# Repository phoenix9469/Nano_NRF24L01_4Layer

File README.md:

## Arduino Nano with DC-DC Converter and NRF24L01 2.4G RF module

### Power IN
XL1509-5.0, Support 5V~45V DC IN  
Reverse Volatege Protection
### Arduino Nano
Atmega328P-AU,FT232RL USB TO UART(USB TYPE C)
### RF module
NORDIC NRF24L01 Transceiver  
SPI communication with Atmega328p  
IPEX antenna connector

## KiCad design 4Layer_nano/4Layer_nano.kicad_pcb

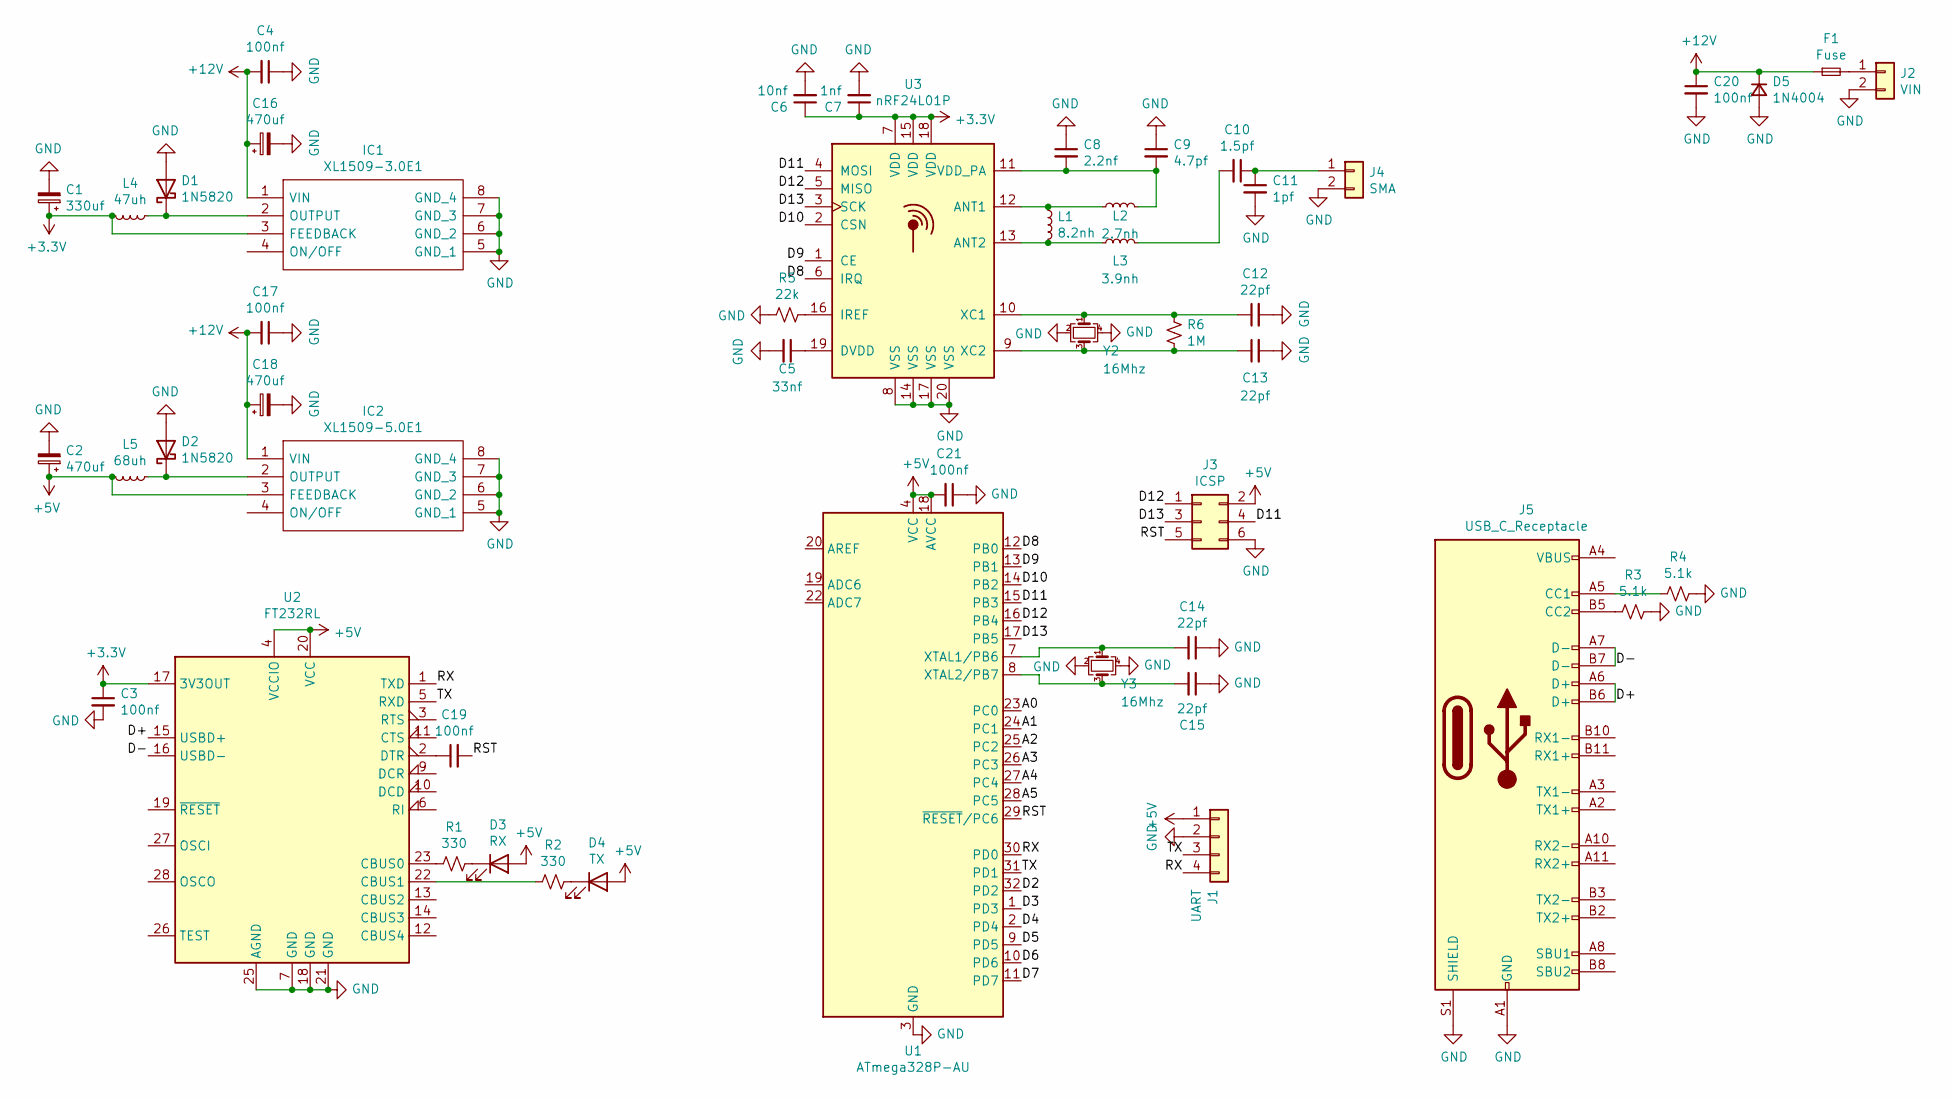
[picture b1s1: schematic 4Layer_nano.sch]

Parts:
C1: 330uf; CP_EIA-7343-31_Kemet-D
C2, C16, C18: 470uf; CP_EIA-7343-31_Kemet-D
C3, C4, C17, C19, C20, C21: 100nf; C_0603_1608Metric
C5: 33nf; C_0402_1005Metric
C6: 10nf; C_0402_1005Metric
C7: 1nf; C_0402_1005Metric
C8: 2.2nf; C_0402_1005Metric
C9: 4.7pf; C_0402_1005Metric
C10: 1.5pf; C_0402_1005Metric
C11: 1pf; C_0402_1005Metric
C12, C13: 22pf; C_0402_1005Metric
C14, C15: 22pf; C_0603_1608Metric
D1, D2: 1N5820; D_SMA
D3: RX; LED_0603_1608Metric
D4: TX; LED_0603_1608Metric
D5: 1N4004; D_SMA
F1: Fuse; FUSC6127X269N
IC1: XL1509-3.0E1; SOIC127P600X175-8N; Manufacturer_Part_Number XL1509-5.0E1
IC2: XL1509-5.0E1; SOIC127P600X175-8N; Manufacturer_Part_Number XL1509-5.0E1
J1: UART; PinHeader_1x04_P2.54mm_Vertical
J2: VIN; TerminalBlock_TE_282834-2_1x02_P2.54mm_Horizontal
J3: ICSP; PinHeader_2x03_P2.54mm_Vertical
J4: SMA; U.FL_Hirose_U.FL-R-SMT-1_Vertical
J5: USB_C_Receptacle; USB_C_Receptacle_HRO_TYPE-C-31-M-12
L1: 8.2nh; L_0402_1005Metric
L2: 2.7nh; L_0402_1005Metric
L3: 3.9nh; L_0402_1005Metric
L4: 47uh; inductor 77
L5: 68uh; inductor 77
R1, R2: 330; R_0603_1608Metric
R3, R4: 5.1k; R_0603_1608Metric
R5: 22k; R_0402_1005Metric
R6: 1M; R_0402_1005Metric
U1: ATmega328P-AU; TQFP-32_7x7mm_P0.8mm
U2: FT232RL; SSOP-28_5.3x10.2mm_P0.65mm
U3: nRF24L01P; QFN-20-1EP_4x4mm_P0.5mm_EP2.5x2.5mm
Y2, Y3: 16Mhz; Crystal_SMD_3225-4Pin_3.2x2.5mm

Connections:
+3V3: C1.1, C3.1, C6.1, C7.1, IC1.3 (FEEDBACK), L4.2, U2.17 (3V3OUT), U3.7 (VDD), U3.15 (VDD), U3.18 (VDD)
+5V: C2.1, C21.2, D3.2 (A), D4.2 (A), IC2.3 (FEEDBACK), J1.1, J3.2, L5.2, U1.4 (VCC), U1.6 (VCC), U1.18 (AVCC), U2.4 (VCCIO), U2.20 (VCC)
+12V: C4.2, C16.1, C17.2, C18.1, C20.1, D5.1 (K), F1.1, IC1.1 (VIN), IC2.1 (VIN)
/A0: U1.23 (PC0)
/A1: U1.24 (PC1)
/A2: U1.25 (PC2)
/A3: U1.26 (PC3)
/A4: U1.27 (PC4)
/A5: U1.28 (PC5)
/D2: U1.32 (PD2)
/D3: U1.1 (PD3)
/D4: U1.2 (PD4)
/D5: U1.9 (PD5)
/D6: U1.10 (PD6)
/D7: U1.11 (PD7)
/D8: U1.12 (PB0), U3.6 (IRQ)
/D9: U1.13 (PB1), U3.1 (CE)
/D10: U1.14 (PB2), U3.2 (CSN)
/D11: J3.4, U1.15 (PB3), U3.4 (MOSI)
/D12: J3.1, U1.16 (PB4), U3.5 (MISO)
/D13: J3.3, U1.17 (PB5), U3.3 (SCK)
/D+: J5.A6 (D+), J5.B6 (D+), U2.15 (USBD+)
/D-: J5.A7 (D-), J5.B7 (D-), U2.16 (USBD-)
/RST: C19.2, J3.5, U1.29 (~RESET~/PC6)
/RX: J1.4, U1.30 (PD0), U2.1 (TXD)
/TX: J1.3, U1.31 (PD1), U2.5 (RXD)
GND: C1.2, C2.2, C3.2, C4.1, C5.2, C6.2, C7.2, C8.1, C9.1, C11.2, C12.2, C13.2, C14.1, C15.1, C16.2, C17.1, C18.2, C20.2, C21.1, D1.2 (A), D2.2 (A), D5.2 (A), IC1.5 (GND_1), IC1.6 (GND_2), IC1.7 (GND_3), IC1.8 (GND_4), IC2.5 (GND_1), IC2.6 (GND_2), IC2.7 (GND_3), IC2.8 (GND_4), J1.2, J2.2, J3.6, J4.2, J5.A1 (GND), J5.A12 (GND), J5.B1 (GND), J5.B12 (GND), J5.S1 (SHIELD), R3.1, R4.1, R5.1, U1.3 (GND), U1.5 (GND), U1.21 (GND), U2.7 (GND), U2.18 (GND), U2.21 (GND), U2.25 (AGND), U3.8 (VSS), U3.14 (VSS), U3.17 (VSS), U3.20 (VSS), Y2.2, Y2.4, Y3.2, Y3.4
unnamed: C5.1, U3.19 (DVDD)
unnamed: C8.2, C9.2, L2.2, U3.11 (VDD_PA)
unnamed: C10.1, C11.1, J4.1
unnamed: C10.2, L3.2
unnamed: C12.1, R6.1, U3.10 (XC1), Y2.1
unnamed: C13.1, R6.2, U3.9 (XC2), Y2.3
unnamed: C14.2, U1.7 (XTAL1/PB6), Y3.1
unnamed: C15.2, U1.8 (XTAL2/PB7), Y3.3
unnamed: C19.1, U2.2 (DTR)
unnamed: D1.1 (K), IC1.2 (OUTPUT), L4.1
unnamed: D2.1 (K), IC2.2 (OUTPUT), L5.1
unnamed: D3.1 (K), R1.2
unnamed: D4.1 (K), R2.2
unnamed: F1.2, J2.1
unnamed: J5.A4 (VBUS), J5.A9 (VBUS), J5.B4 (VBUS), J5.B9 (VBUS)
unnamed: J5.A5 (CC1), R4.2
unnamed: J5.B5 (CC2), R3.2
unnamed: L1.1, L2.1, U3.12 (ANT1)
unnamed: L1.2, L3.1, U3.13 (ANT2)
unnamed: R1.1, U2.23 (CBUS0)
unnamed: R2.1, U2.22 (CBUS1)
unnamed: R5.2, U3.16 (IREF)

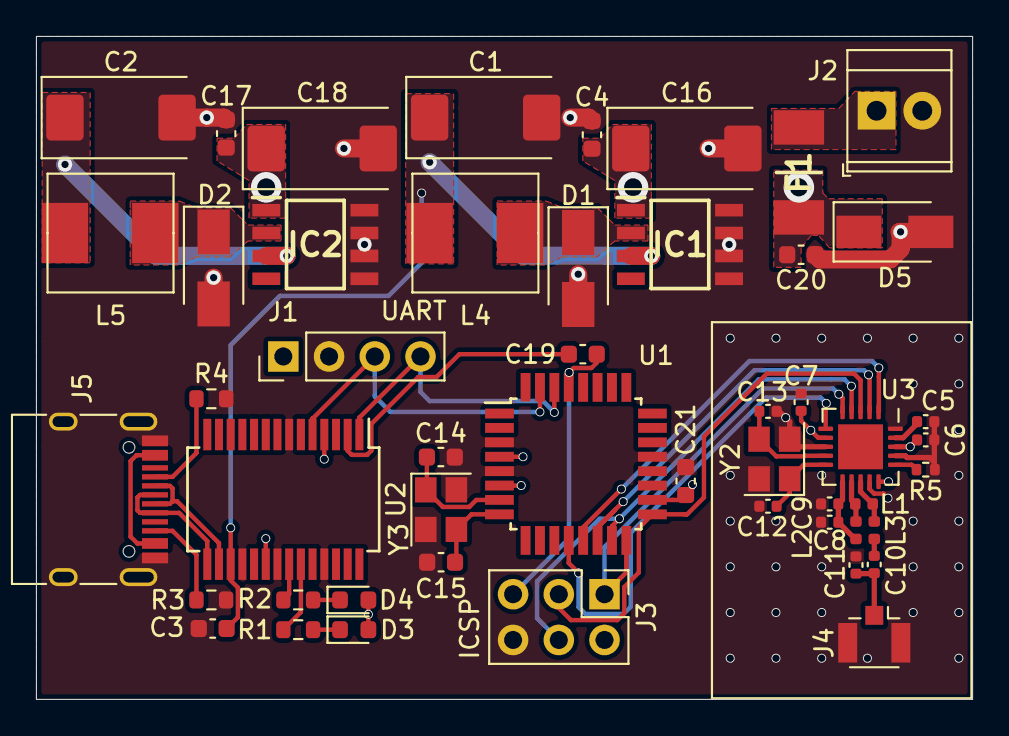
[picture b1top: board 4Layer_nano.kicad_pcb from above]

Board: 4 copper layers, 52.0 x 36.8 mm, 49 parts (0 on the bottom side), 37 nets.

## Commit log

2022-05-18 Kicad File
2022-05-18 Image
